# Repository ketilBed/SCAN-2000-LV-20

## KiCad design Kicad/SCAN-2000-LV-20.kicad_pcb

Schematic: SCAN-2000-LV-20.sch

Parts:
C1: 100n; C_0805_2012Metric_Pad1.18x1.45mm_HandSolder
C2: 4.7u; C_0805_2012Metric_Pad1.18x1.45mm_HandSolder
C3, C6, C7, C11, C44, C47: 10u; C_0805_2012Metric_Pad1.18x1.45mm_HandSolder
C4, C5, C8, C10, C45, C46: 1u; C_0805_2012Metric_Pad1.18x1.45mm_HandSolder
C9, C12, C13, C14, C15, C16, C17, C18, C19, C20, C21, C23, C24, C25, C26, C27, C28, C29, C30, C31, C32, C33, C34, C35, C36, C37, C38, C39, C40, C41, C42, C43: 0.1u; C_0805_2012Metric_Pad1.18x1.45mm_HandSolder
C22: 100u; C_0805_2012Metric_Pad1.18x1.45mm_HandSolder
D1, D2, D3, D4, D5, D6, D7, D8, D9, D10, D11, D12, D13, D14, D15, D16, D17, D18, D19, D20, D21, D22, D23, D24, D25, D26, D27, D28, D29, D30, D31, D32, D33, D34, D35, D36, D37, D38, D39, D40: BAV199L; SOT-23
D41, D42, D43, D44: LED; R_0805_2012Metric_Pad1.20x1.40mm_HandSolder
H1, H2: MountingHole; MountingHole_3.2mm_M3_DIN965_Pad
J1: FTDI; PinSocket_1x06_P2.54mm_Vertical
J2, J3: Conn_01x02; PinSocket_1x02_P2.54mm_Vertical
J4, J6: BUS-A-INPUT; TerminalBlock_Phoenix_MKDS-1,5-10-5.08_1x10_P5.08mm_Horizon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
J5: SWD; PinSocket_1x06_P2.54mm_Vertical
J7, J8: BUS-B-INPUT; TerminalBlock_Phoenix_MKDS-1,5-10-5.08_1x10_P5.08mm_Horizon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
J9: MOLEX 85050-0000; DIN41612_B2_2x16_Male_Horizontal_THT
J10: OUTPUT-BUS-A; TerminalBlock_Phoenix_MKDS-1,5-2-5.08_1x02_P5.08mm_Horizont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
J11: OUTPUT-BUS-B; TerminalBlock_Phoenix_MKDS-1,5-2-5.08_1x02_P5.08mm_Horizont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
J12: Test; PinSocket_1x09_P2.54mm_Vertical
J13: Conn_02x04_Counter_Clockwise; PinSocket_2x04_P2.54mm_Vertical
K1: EC2-3TNU; Relay_DPDT_Kemet_EC2_DoubleCoil
L1, L2, L3: L; L_0805_2012Metric_Pad1.15x1.40mm_HandSolder
R1, R2, R3, R4, R5, R6, R7, R8, R9, R10, R11, R12, R13, R14, R15, R16, R17, R18, R19, R20: R; R_2512_6332Metric_Pad1.40x3.35mm_HandSolder
R21, R22, R23, R24: R; R_0805_2012Metric_Pad1.20x1.40mm_HandSolder
U1: STM32G030; LQFP-32_7x7mm_P0.8mm
U2, U3, U4, U5, U6, U7, U8, U9, U10, U11: DG412; SOIC-16_3.9x9.9mm_P1.27mm
U12: RB-0515D
U13, U16: MDC3105; SOT-23
U14: TPS78233DDC; SOT-23-5
U15: TL7733BD; SOIC-8_3.9x4.9mm_P1.27mm
U17: RB-0505S; RB-0515D

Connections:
+3V3: C1.1, C2.1, C9.1, C11.1, J2.1, J3.1, J12.5, R21.1, U1.4 (Vdd), U14.5 (OUT), U15.7 (SENSE), U15.8 (VCC)
+VDC: C46.1, C47.1, J13.1, J13.2, J13.7, J13.8, U17.1
-15V: C7.2, C8.2, C24.2, C25.2, C26.2, C27.2, C28.2, C39.2, C40.2, C41.2, C42.2, C43.2, D1.1 (K), D2.1 (K), D3.1 (K), D4.1 (K), D5.1 (K), D6.1 (K), D7.1 (K), D8.1 (K), D9.1 (K), D10.1 (K), D11.1 (K), D12.1 (K), D13.1 (K), D14.1 (K), D15.1 (K), D16.1 (K), D17.1 (K), D18.1 (K), D19.1 (K), D20.1 (K), D21.1 (K), D22.1 (K), D23.1 (K), D24.1 (K), D25.1 (K), D26.1 (K), D27.1 (K), D28.1 (K), D29.1 (K), D30.1 (K), D31.1 (K), D32.1 (K), D33.1 (K), D34.1 (K), D35.1 (K), D36.1 (K), D37.1 (K), D38.1 (K), D39.1 (K), D40.1 (K), D41.1 (K), J12.2, L2.2, U2.4 (V-), U3.4 (V-), U4.4 (V-), U5.4 (V-), U6.4 (V-), U7.4 (V-), U8.4 (V-), U9.4 (V-), U10.4 (V-), U11.4 (V-)
BUS-A-HI: J10.1, K1.3, U2.2, U2.10, U3.2, U3.10, U4.2, U4.10, U5.2, U5.10, U6.2, U6.10
BUS-A-LO: J10.2, K1.10, U2.6, U2.15, U3.6, U3.15, U4.6, U4.15, U5.6, U5.15, U6.6, U6.15
BUS-B-HI: K1.4, U7.6, U7.15, U8.6, U8.15, U9.6, U9.15, U10.6, U10.15, U11.6, U11.15
BUS-B-LO: K1.9, U7.2, U7.10, U8.2, U8.10, U9.2, U9.10, U10.2, U10.10, U11.2, U11.10
BUS-RESET: U1.19 (PA9), U13.1
BUS-SET: U1.20 (PC6), U16.1
CHAN-01A-CON: U1.32 (PB8), U2.9, U2.16
CHAN-01A-HI: D1.3 (K), J4.1, R1.2, U2.11
CHAN-01A-LO: D2.3 (K), J4.2, R1.1, U2.14
CHAN-01B-CON: U1.7 (PA0), U7.1, U7.8
CHAN-01B-HI: D21.3 (K), J7.10, R11.2, U7.7
CHAN-01B-LO: D22.3 (K), J7.9, R11.1, U7.3
CHAN-02A-CON: U1.31 (PB7), U2.1, U2.8
CHAN-02A-HI: D3.3 (K), J4.3, R2.2, U2.3
CHAN-02A-LO: D4.3 (K), J4.4, R2.1, U2.7
CHAN-02B-CON: U1.8 (PA1), U7.9, U7.16
CHAN-02B-HI: D23.3 (K), J7.8, R12.2, U7.14
CHAN-02B-LO: D24.3 (K), J7.7, R12.1, U7.11
CHAN-03A-CON: U1.30 (PB6), U3.9, U3.16
CHAN-03A-HI: D5.3 (K), J4.5, R3.2, U3.11
CHAN-03A-LO: D6.3 (K), J4.6, R3.1, U3.14
CHAN-03B-CON: U1.11 (PA4), U8.1, U8.8
CHAN-03B-HI: D25.3 (K), J7.6, R13.2, U8.7
CHAN-03B-LO: D26.3 (K), J7.5, R13.1, U8.3
CHAN-04A-CON: U1.29 (PB5), U3.1, U3.8
CHAN-04A-HI: D7.3 (K), J4.7, R4.2, U3.3
CHAN-04A-LO: D8.3 (K), J4.8, R4.1, U3.7
CHAN-04B-CON: U1.12 (PA5), U8.9, U8.16
CHAN-04B-HI: D27.3 (K), J7.4, R14.2, U8.14
CHAN-04B-LO: D28.3 (K), J7.3, R14.1, U8.11
CHAN-05A-CON: U1.28 (PB4), U4.9, U4.16
CHAN-05A-HI: D9.3 (K), J4.9, R5.2, U4.11
CHAN-05A-LO: D10.3 (K), J4.10, R5.1, U4.14
CHAN-05B-CON: U1.13 (PA6), U9.1, U9.8
CHAN-05B-HI: D29.3 (K), J7.2, R15.2, U9.7
CHAN-05B-LO: D30.3 (K), J7.1, R15.1, U9.3
CHAN-06A-CON: U1.27 (PB3), U4.1, U4.8
CHAN-06A-HI: D11.3 (K), J6.1, R6.2, U4.3
CHAN-06A-LO: D12.3 (K), J6.2, R6.1, U4.7
CHAN-06B-CON: U1.14 (PA7), U9.9, U9.16
CHAN-06B-HI: D31.3 (K), J8.10, R16.2, U9.14
CHAN-06B-LO: D32.3 (K), J8.9, R16.1, U9.11
CHAN-07A-CON: U1.24 (PA13), U5.9, U5.16
CHAN-07A-HI: D13.3 (K), J6.3, R7.2, U5.11
CHAN-07A-LO: D14.3 (K), J6.4, R7.1, U5.14
CHAN-07B-CON: U1.15 (PB0), U10.1, U10.8
CHAN-07B-HI: D33.3 (K), J8.8, R17.2, U10.7
CHAN-07B-LO: D34.3 (K), J8.7, R17.1, U10.3
CHAN-08A-CON: U1.23 (PA12), U5.1, U5.8
CHAN-08A-HI: D15.3 (K), J6.5, R8.2, U5.3
CHAN-08A-LO: D16.3 (K), J6.6, R8.1, U5.7
CHAN-08B-CON: U1.16 (PB1), U10.9, U10.16
CHAN-08B-HI: D35.3 (K), J8.6, R18.2, U10.14
CHAN-08B-LO: D36.3 (K), J8.5, R18.1, U10.11
CHAN-09A-CON: U1.22 (PA11), U6.9, U6.16
CHAN-09A-HI: D17.3 (K), J6.7, R9.2, U6.11
CHAN-09A-LO: D18.3 (K), J6.8, R9.1, U6.14
CHAN-09B-CON: U1.17 (PB2), U11.1, U11.8
CHAN-09B-HI: D37.3 (K), J8.4, R19.2, U11.7
CHAN-09B-LO: D38.3 (K), J8.3, R19.1, U11.3
CHAN-10A-CON: U1.21 (PA10), U6.1, U6.8
CHAN-10A-HI: D19.3 (K), J6.9, R10.2, U6.3
CHAN-10A-LO: D20.3 (K), J6.10, R10.1, U6.7
CHAN-10B-CON: U1.18 (PA8), U11.9, U11.16
CHAN-10B-HI: D39.3 (K), J8.2, R20.2, U11.14
CHAN-10B-LO: D40.3 (K), J8.1, R20.1, U11.11
CLOCK: J9.a4, J9.b4, J12.7, U1.2 (PC14)
CTS: J1.5
DATA: J9.a2, J9.a13, J9.b2, J12.6, U1.3 (PC15)
DTR: J1.1
GND: C1.2, C2.2, C3.2, C4.2, C5.2, C6.2, C7.1, C8.1, C9.2, C10.2, C11.2, C12.2, C13.2, C14.2, C15.2, C16.2, C17.2, C18.2, C19.2, C20.2, C21.2, C22.2, C23.2, C24.1, C25.1, C26.1, C27.1, C28.1, C29.2, C30.2, C31.2, C32.2, C33.2, C34.2, C35.2, C36.2, C37.2, C38.2, C39.1, C40.1, C41.1, C42.1, C43.1, C44.2, C45.2, D42.1 (K), D43.1 (K), D44.1 (K), J1.6, J5.3, J9.a1, J9.a3, J9.a5, J9.a7, J9.a14, J9.a15, J9.a16, J9.b1, J9.b3, J9.b5, J9.b7, J9.b13, J9.b14, J9.b15, J9.b16, J12.1, R24.1, U1.5 (Vss), U2.5 (GND), U3.5 (GND), U4.5 (GND), U5.5 (GND), U6.5 (GND), U7.5 (GND), U8.5 (GND), U9.5 (GND), U10.5 (GND), U11.5 (GND), U12.2, U12.5, U13.2, U14.2 (GND), U14.4 (GND), U15.4 (GND), U16.2, U17.5
GNDPWR: C46.2, C47.2, J13.3, J13.4, J13.5, J13.6, U17.2
NRST: J5.5, U1.6 (NRST), U15.5 (~RESET)
unnamed: C22.1, U15.3 (CT)
unnamed: C23.1, U15.1 (REF)
unnamed: D41.2 (A), R24.2
unnamed: D42.2 (A), R21.2
unnamed: D43.2 (A), R22.2
unnamed: D44.2 (A), R23.2
unnamed: J1.4, J2.2
unnamed: J3.2, J5.1
unnamed: J11.1, K1.8
unnamed: J11.2, K1.5
unnamed: K1.7, U13.3
unnamed: K1.12, U16.3
unnamed: L1.1, U12.6
unnamed: L2.1, U12.4
unnamed: L3.1, U17.6
RESET: J9.a8, J9.b8, J12.9, U15.2 (~RESIN)
STROBE: J9.a6, J9.b6, J12.8, U1.1 (PB9)
SWCLK: J5.2, U1.26 (PA15)
SWDIO: J5.4, U1.25 (PA14)
SWO: J5.6
USART_1_RX: J1.2, U1.10 (PA3)
USART_1_TX: J1.3, U1.9 (PA2)

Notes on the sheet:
Isolated Input
R1 Through R20 Optional Current Shunt.

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
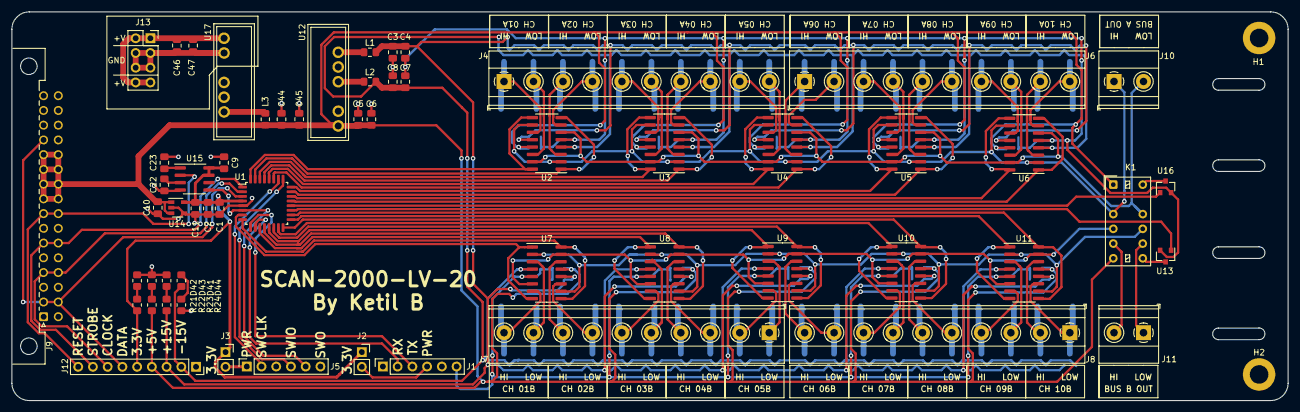
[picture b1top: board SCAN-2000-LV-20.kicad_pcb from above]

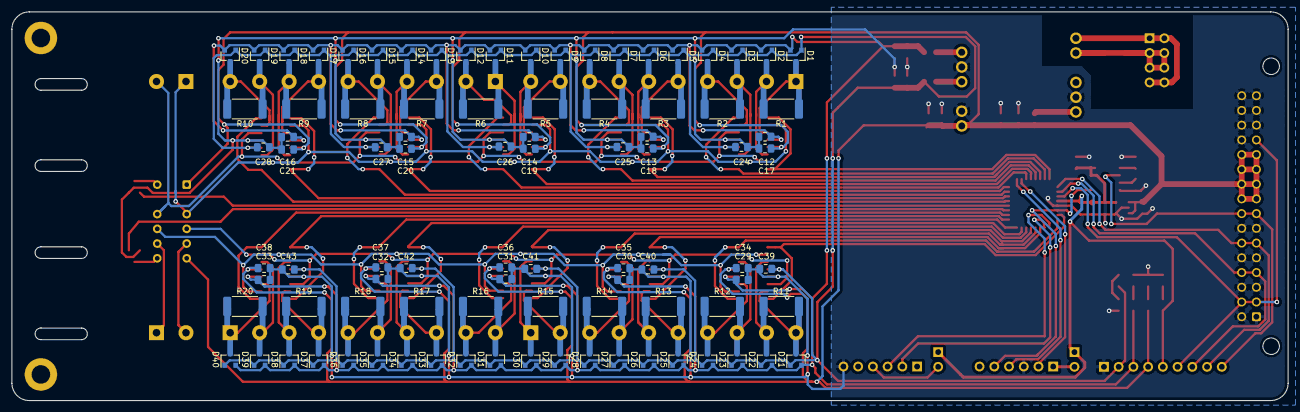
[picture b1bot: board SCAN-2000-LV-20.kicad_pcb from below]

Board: 2 copper layers, 220.0 x 67.0 mm, 151 parts (90 on the bottom side), 97 nets.

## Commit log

2020-12-08 Replaced DG412s with DG409s
    Replaced the DG412s with DG409s. This reduces the leakage current form
    the switches to +-1nA per device. Also reduces the number of control
    lines to 10. Settled on an overvolt protection scheme. Blocking diodes
    on the supply lines for the DG409s, as per the data covering, and rail
    clamping diodes with current limiting resistors.
    As an overvolt condition starts, the protection diodes in the DG409s
2020-12-12 Board layout for the Switches
